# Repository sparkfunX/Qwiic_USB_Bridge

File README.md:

SparkFun Qwiic USB Development Kit - SAMD21
========================================

[*Qwiic USB Development Kit - SAMD21 (SPX-24639)*](https://www.sparkfun.com/products/24639)

The Qwiic USB Development kit is designed for folks that want to interface a Qwiic device quickly and easily to a computer. The core processor is the SAM21 which allows quick (hah!) and seamless serial printing over USB, as well as easy development and programming using the Arduino environment. The professional printed enclosure makes the device easy to plug/unplug as well as allowing Qwiic boards to be mounted to the enclosure itself.

The development kit features two Qwiic connectors and a user-addressable WS2812 LED. In case you need more IO, there are four GPIO pins, accessible by removing the enclosure, two of which are ADC pins. This little device is not only a great tool for making compact prototypes, but a handy way to add Qwiic sensors to your PC-based projects.

Repository Contents
-------------------

* **/Documentation** - Data sheets, additional product information
* **/Enclosure** - Enclosure files 
* **/Firmware** - Example code 
* **/Hardware** - Eagle design files (.brd, .sch)
* **/Production** - Production panel files (.brd)

License Information
-------------------

This product is _**open source**_! 

Please review the LICENSE.md file for license information. 

If you have any questions or concerns on licensing, please contact technical support on our [SparkFun forums](https://forum.sparkfun.com/viewforum.php?f=152).

Distributed as-is; no warranty is given.

- Your friends at SparkFun.

_<COLLABORATION CREDIT>_

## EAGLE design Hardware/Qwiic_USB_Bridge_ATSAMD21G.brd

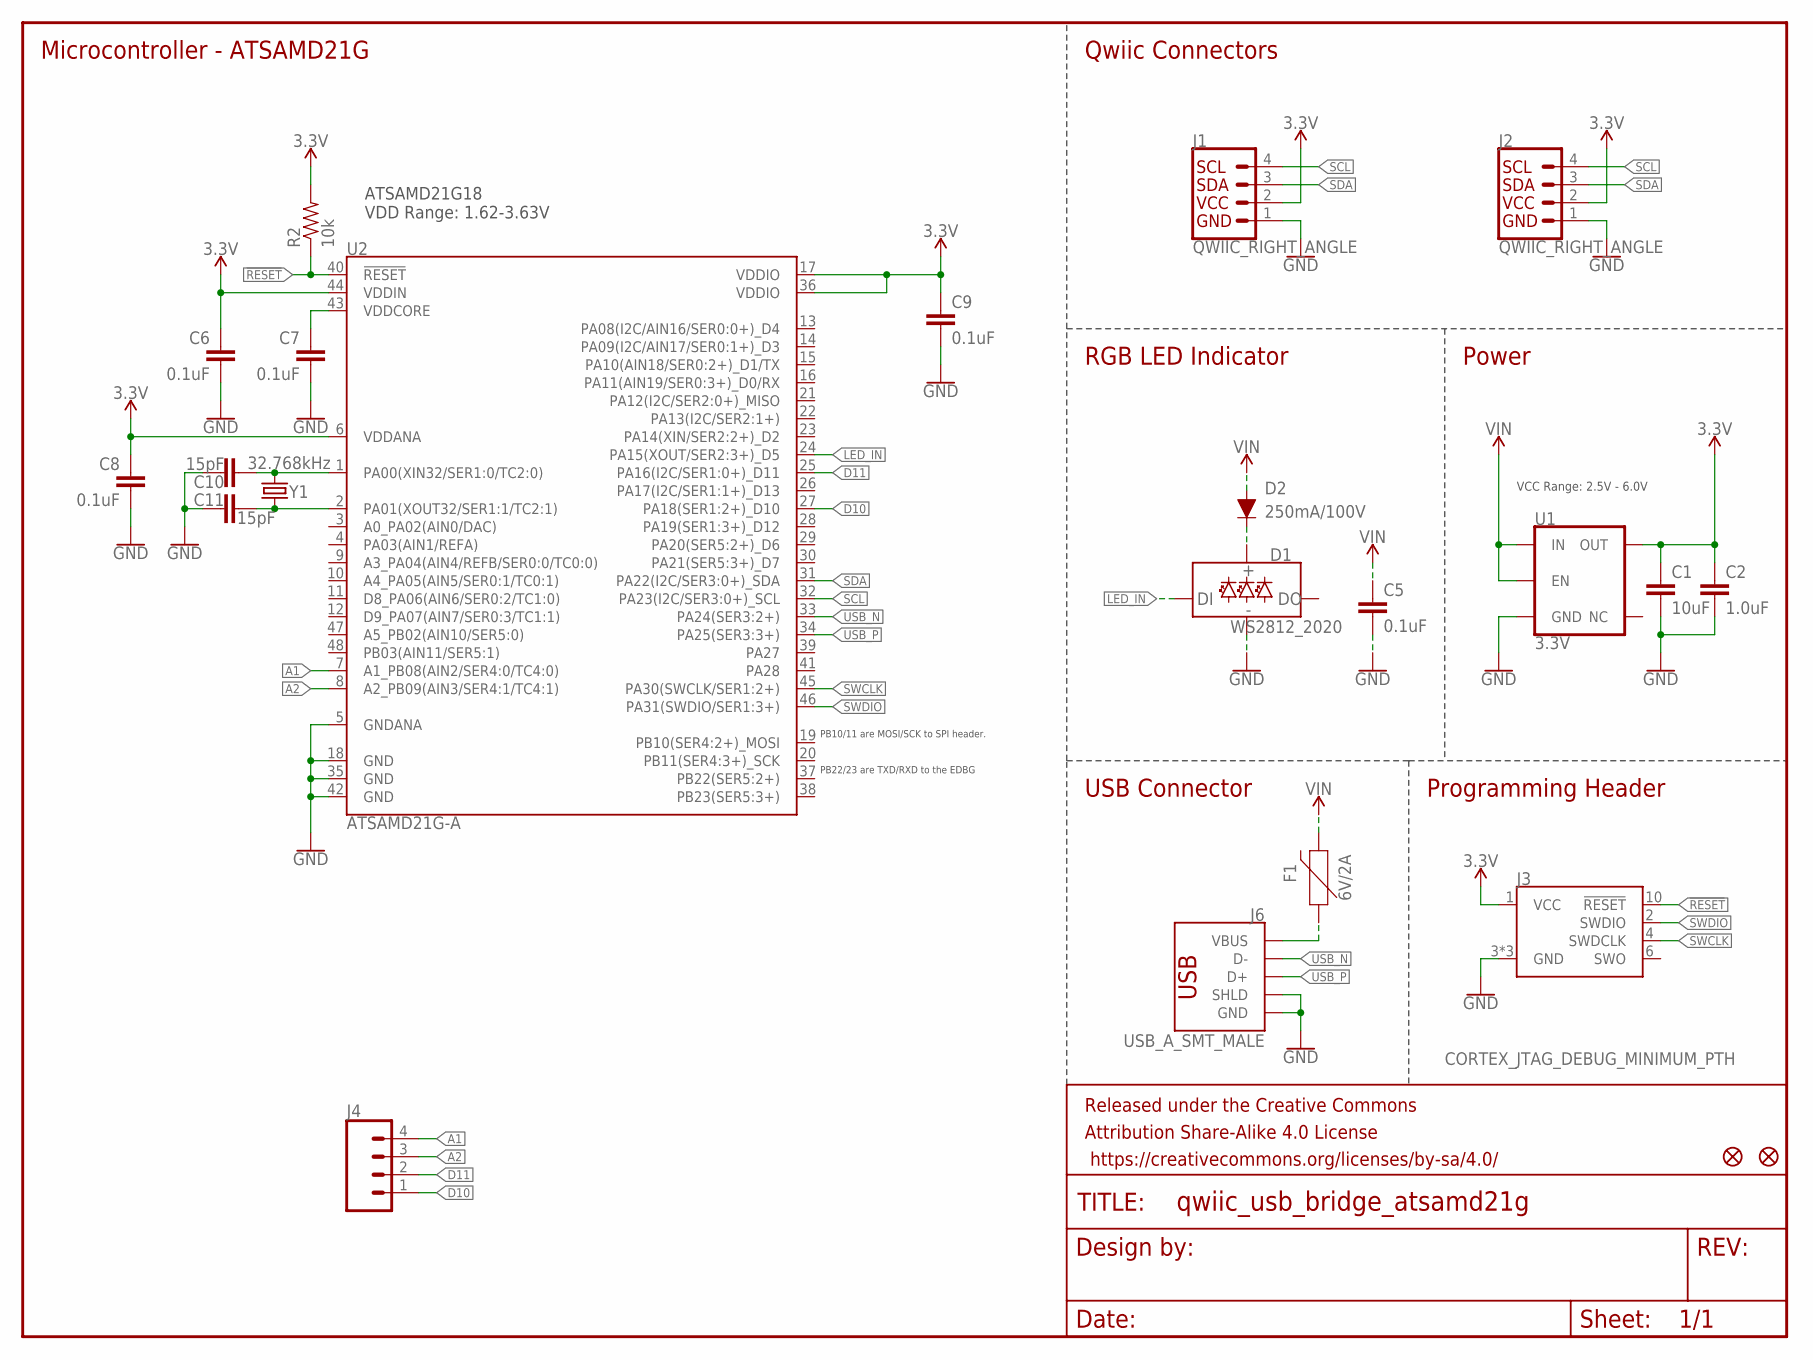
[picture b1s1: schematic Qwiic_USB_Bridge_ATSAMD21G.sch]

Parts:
C1: 10uF; 0603
C2: 1.0uF; 0603
C5, C6, C7, C8, C9: 0.1uF; 0603
C10, C11: 15pF; 0603
D1: WS2812_2020; WS2812-2020
D2: 250mA/100V; SOD-323
F1: 6V/2A; 1210
FD1, FD2: FIDUCIALUFIDUCIAL; FIDUCIAL-MICRO
FRAME2: FRAME-LETTER; CREATIVE_COMMONS
J1, J2: QWIIC_RIGHT_ANGLE; JST04_1MM_RA
J3: CORTEX_JTAG_DEBUG_MINIMUM_PTH; 2X5-PTH-1.27MM
J4: CONN_041X04_NO_SILK; 1X04_NO_SILK
J6: USB_A_SMT_MALE; USB-A-SMT-MALE
R2: 10k; 0603
U1: 3.3V; SOT23-5
U2: ATSAMD21G-A; TQFP-48
Y1: 32.768kHz; CRYSTAL-SMD-3.2X1.5MM

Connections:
3.3V: C1.1, C2.1, C6.1, C8.1, C9.1, J1.2, J2.2, J3.1 (VCC), R2.2, U1.5 (OUT), U2.6 (VDDANA), U2.17 (VDDIO), U2.36 (VDDIO), U2.44 (VDDIN)
!RESET: J3.10 (!RESET), R2.1, U2.40 (!RESET!)
A1: J4.4, U2.7 (A1_PB08(AIN2/SER4:0/TC4:0))
A2: J4.3, U2.8 (A2_PB09(AIN3/SER4:1/TC4:1))
D10: J4.1, U2.27 (PA18(SER1:2+)_D10)
D11: J4.2, U2.25 (PA16(I2C/SER1:0+)_D11)
GND: C1.2, C2.2, C5.2, C6.2, C7.2, C8.2, C9.2, C10.1, C11.2, D1.GND, J1.1, J2.1, J3.3 (GND), J3.5 (GND), J3.9 (GND), J6.GND1 (GND), J6.SHLD1 (SHLD), J6.SHLD2 (SHLD), U1.2 (GND), U2.5 (GNDANA), U2.18 (GND), U2.35 (GND), U2.42 (GND)
LED_IN: D1.DI, U2.24 (PA15(XOUT/SER2:3+)_D5)
unnamed: F1.1, J6.VBUS1 (VBUS)
unnamed: D1.VCC, D2.C
unnamed: C10.2, U2.1 (PA00(XIN32/SER1:0/TC2:0)), Y1.P$2 (2)
unnamed: C11.1, U2.2 (PA01(XOUT32/SER1:1/TC2:1)), Y1.P$1 (1)
SCL: J1.4, J2.4, U2.32 (PA23(I2C/SER3:0+)_SCL)
SDA: J1.3, J2.3, U2.31 (PA22(I2C/SER3:0+)_SDA)
SWCLK: J3.4 (SWDCLK), U2.45 (PA30(SWCLK/SER1:2+))
SWDIO: J3.2 (SWDIO), U2.46 (PA31(SWDIO/SER1:3+))
USB_N: J6.D-1 (D-), U2.33 (PA24(SER3:2+))
USB_P: J6.D+1 (D+), U2.34 (PA25(SER3:3+))
VDDCORE1: C7.1, U2.43 (VDDCORE)
VIN: C5.1, D2.A, F1.2, U1.1 (IN), U1.3 (EN)

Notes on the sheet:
Qwiic Connectors
RGB LED Indicator
Power
Microcontroller - ATSAMD21G
VCC Range: 2.5V - 6.0V
USB Connector
Programming Header
PB22/23 are TXD/RXD to the EDBG
PB10/11 are MOSI/SCK to SPI header.
ATSAMD21G18 VDD Range: 1.62-3.63V

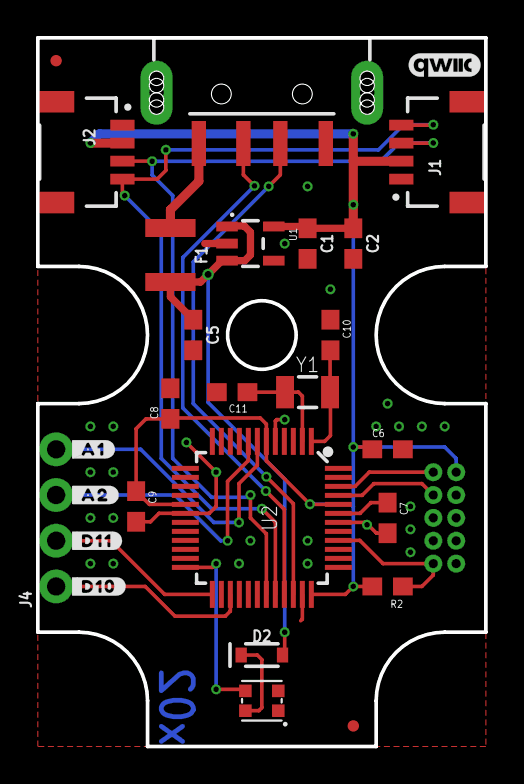
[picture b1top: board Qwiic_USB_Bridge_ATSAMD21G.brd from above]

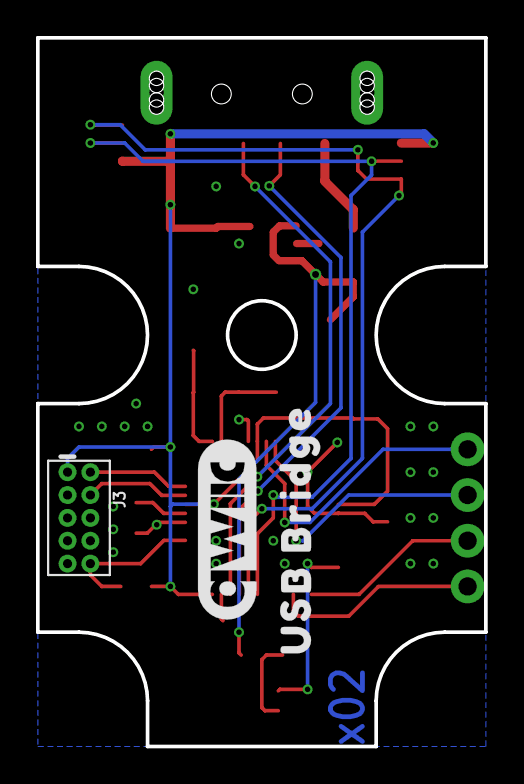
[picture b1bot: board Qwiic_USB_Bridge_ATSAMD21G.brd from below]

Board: 2 copper layers, 24.9 x 39.4 mm, 31 parts (3 on the bottom side), 20 nets.

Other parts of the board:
U$1: #_A1#0
U$2: #_A2#0
U$3: #_D11#0
U$4: #_D10#0
U$7: QWIIC_10MM
U$8: USB_BRIDGE0
U$9: QWIIC_4MM

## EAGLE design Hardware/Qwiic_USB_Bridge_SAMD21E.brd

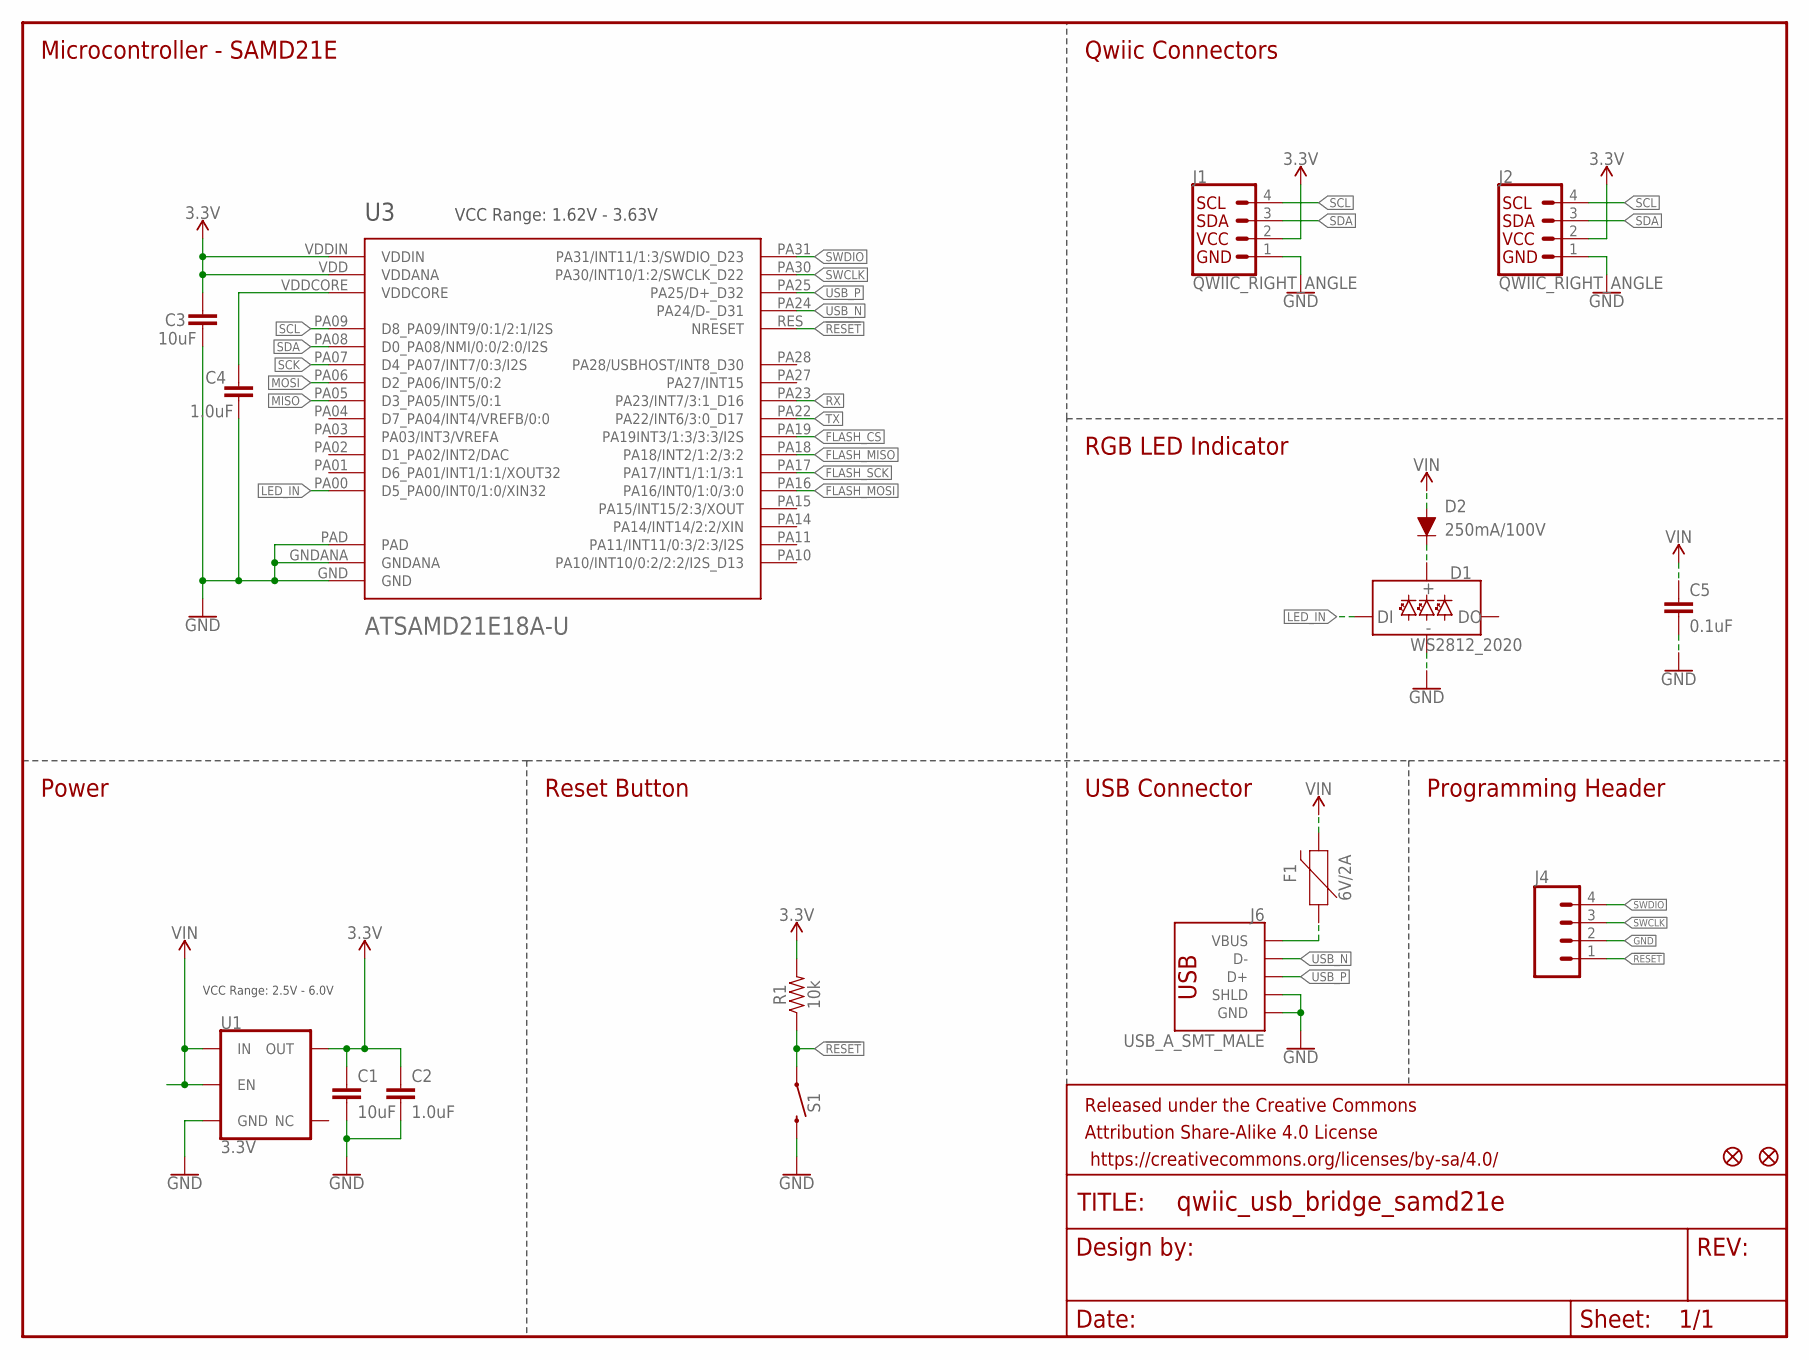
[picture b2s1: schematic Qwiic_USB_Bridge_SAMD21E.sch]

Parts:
C1, C3: 10uF; 0603
C2, C4: 1.0uF; 0402
C5: 0.1uF; 0603
D1: WS2812_2020; WS2812-2020
D2: 250mA/100V; SOD-323
F1: 6V/2A; 1210
FD1, FD2: FIDUCIALUFIDUCIAL; FIDUCIAL-MICRO
FRAME2: FRAME-LETTER; CREATIVE_COMMONS
J1, J2: QWIIC_RIGHT_ANGLE; JST04_1MM_RA
J4: CONN_041.27MM_NO_SILK; 1X04_1.27MM_NO_SILK
J6: USB_A_SMT_MALE; USB-A-SMT-MALE
R1: 10k; 0603
S1: MOMENTARY-SWITCH-SPST-SMD-6.0X3.5MM; TACTILE_SWITCH_SMD_6.0X3.5MM
U1: 3.3V; SOT23-5
U3: ATSAMD21E18A-U; QFN-32_SAMD

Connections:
3.3V: C1.1, C2.1, C3.1, J1.2, J2.2, R1.2, U1.5 (OUT), U3.VDD (VDDANA), U3.VDDIN
!RESET: J4.1, R1.1, S1.1, U3.RES (NRESET)
FLASH_CS: U3.PA19 (PA19INT3/1:3/3:3/I2S)
FLASH_MISO: U3.PA18 (PA18/INT2/1:2/3:2)
FLASH_MOSI: U3.PA16 (PA16/INT0/1:0/3:0)
FLASH_SCK: U3.PA17 (PA17/INT1/1:1/3:1)
GND: C1.2, C2.2, C3.2, C4.1, C5.2, D1.GND, J1.1, J2.1, J4.2, J6.GND1 (GND), J6.SHLD1 (SHLD), J6.SHLD2 (SHLD), S1.2, U1.2 (GND), U3.GND, U3.GNDANA, U3.PAD
LED_IN: D1.DI, U3.PA00 (D5_PA00/INT0/1:0/XIN32)
MISO: U3.PA05 (D3_PA05/INT5/0:1)
MOSI: U3.PA06 (D2_PA06/INT5/0:2)
unnamed: F1.1, J6.VBUS1 (VBUS)
unnamed: D1.VCC, D2.C
RX: U3.PA23 (PA23/INT7/3:1_D16)
SCK: U3.PA07 (D4_PA07/INT7/0:3/I2S)
SCL: J1.4, J2.4, U3.PA09 (D8_PA09/INT9/0:1/2:1/I2S)
SDA: J1.3, J2.3, U3.PA08 (D0_PA08/NMI/0:0/2:0/I2S)
SWCLK: J4.3, U3.PA30 (PA30/INT10/1:2/SWCLK_D22)
SWDIO: J4.4, U3.PA31 (PA31/INT11/1:3/SWDIO_D23)
TX: U3.PA22 (PA22/INT6/3:0_D17)
USB_N: J6.D-1 (D-), U3.PA24 (PA24/D-_D31)
USB_P: J6.D+1 (D+), U3.PA25 (PA25/D+_D32)
VDDCORE: C4.2, U3.VDDCORE
VIN: C5.1, D2.A, F1.2, U1.1 (IN), U1.3 (EN)

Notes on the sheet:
Qwiic Connectors
RGB LED Indicator
Power
Microcontroller - SAMD21E
VCC Range: 2.5V - 6.0V
VCC Range: 1.62V - 3.63V
Reset Button
USB Connector
Programming Header

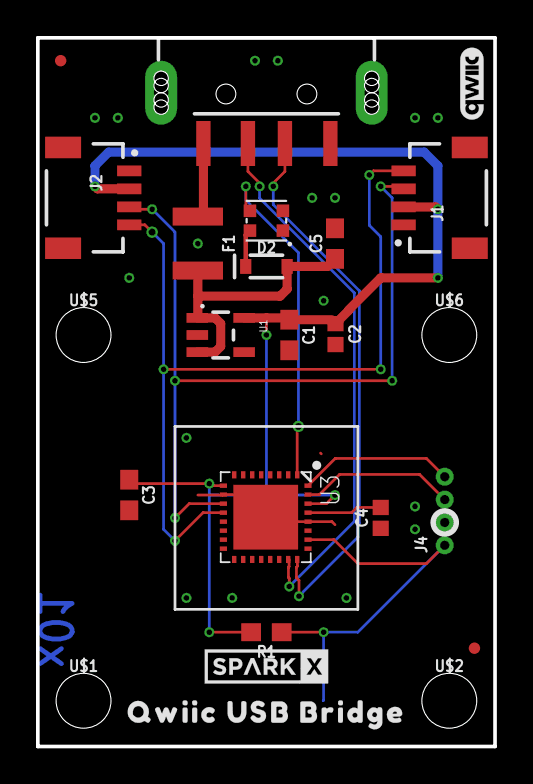
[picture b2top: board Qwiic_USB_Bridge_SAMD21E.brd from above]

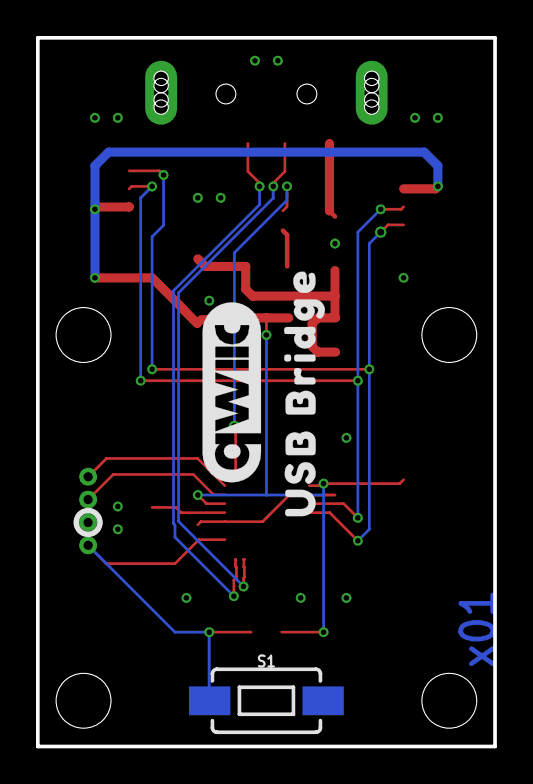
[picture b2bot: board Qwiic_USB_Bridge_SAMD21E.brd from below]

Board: 2 copper layers, 25.4 x 39.4 mm, 28 parts (3 on the bottom side), 14 nets.

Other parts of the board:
U$1, U$2, U$5, U$6: STAND-OFF-TIGHT
U$3: QWIIC_USB_BRIDGE0
U$4: SPARKX-SMALL
U$7: QWIIC_10MM
U$8: USB_BRIDGE0
U$9: QWIIC_4MM

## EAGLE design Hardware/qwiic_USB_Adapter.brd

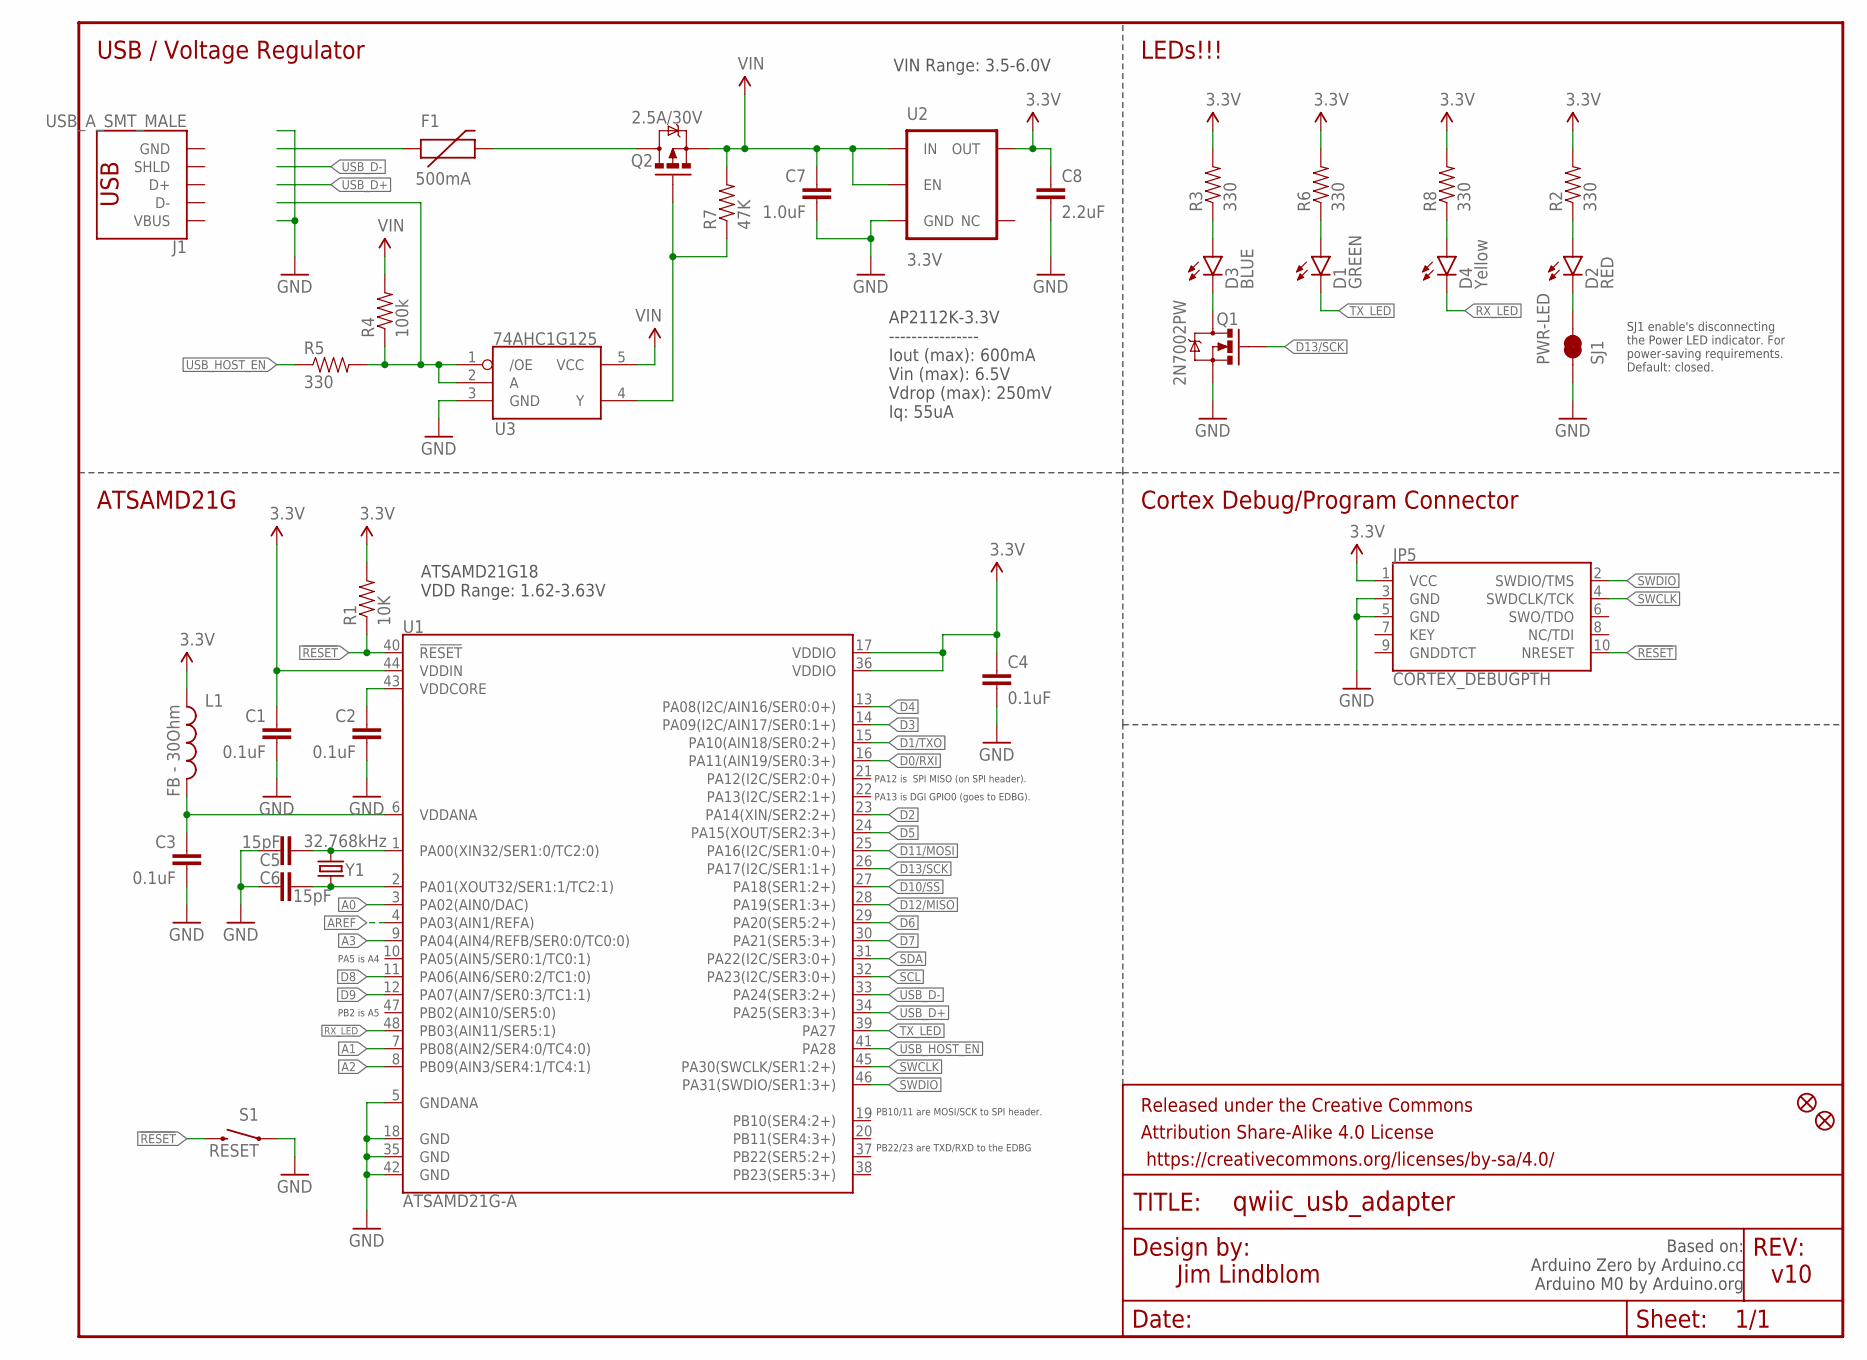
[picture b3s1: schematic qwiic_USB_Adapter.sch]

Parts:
C1, C2, C3, C4: 0.1uF; 0402-CAP
C5, C6: 15pF; 0402-CAP
C7: 1.0uF; 0805-CAP
C8: 2.2uF; 0603-CAP
D1: GREEN; LED-0603
D2: RED; LED-0603
D3: BLUE; LED-0603
D4: Yellow; LED-0603
F1: 500mA; PTC-1206
FID1, FID2: FIDUCIAL1X2; FIDUCIAL-1X2
FRAME1: FRAME-LETTER; CREATIVE_COMMONS
J1: USB_A_SMT_MALE; USB-A-SMT-MALE
JP5: CORTEX_DEBUGPTH; 2X5-PTH-1.27MM
L1: FB - 30Ohm; 0603
Q1: 2N7002PW; SOT323
Q2: 2.5A/30V; SOT23-3
R1: 10K; 0603-RES
R2, R3, R5, R6, R8: 330; 0603-RES
R4: 100k; 0603-RES
R7: 47K; 0603-RES
S1: RESET; TACTILE_SWITCH_SMD_4.6X2.8MM
SJ1: PWR-LED; PAD-JUMPER-2-NC_BY_TRACE_NO_SILK
U1: ATSAMD21G-A; TQFP-48
U2: 3.3V; SOT23-5
U3: 74AHC1G125; SOT23-5
Y1: 32.768kHz; CRYSTAL-SMD-3.2X1.5MM

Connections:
3.3V: C1.1, C4.1, C8.1, JP5.1 (VCC), L1.1, R1.2, R2.2, R3.2, R6.2, R8.2, U1.17 (VDDIO), U1.36 (VDDIO), U1.44 (VDDIN), U2.5 (OUT)
!RESET: JP5.10 (NRESET), R1.1, S1.3 (2), S1.4 (2), U1.40 (!RESET!)
A0: U1.3 (PA02(AIN0/DAC))
A1: U1.7 (PB08(AIN2/SER4:0/TC4:0))
A2: U1.8 (PB09(AIN3/SER4:1/TC4:1))
A3: U1.9 (PA04(AIN4/REFB/SER0:0/TC0:0))
AREF: U1.4 (PA03(AIN1/REFA))
D0/RXI: U1.16 (PA11(AIN19/SER0:3+))
D1/TXO: U1.15 (PA10(AIN18/SER0:2+))
D2: U1.23 (PA14(XIN/SER2:2+))
D3: U1.14 (PA09(I2C/AIN17/SER0:1+))
D4: U1.13 (PA08(I2C/AIN16/SER0:0+))
D5: U1.24 (PA15(XOUT/SER2:3+))
D6: U1.29 (PA20(SER5:2+))
D7: U1.30 (PA21(SER5:3+))
D8: U1.11 (PA06(AIN6/SER0:2/TC1:0))
D9: U1.12 (PA07(AIN7/SER0:3/TC1:1))
D10/SS: U1.27 (PA18(SER1:2+))
D11/MOSI: U1.25 (PA16(I2C/SER1:0+))
D12/MISO: U1.28 (PA19(SER1:3+))
D13/SCK: Q1.1 (G), U1.26 (PA17(I2C/SER1:1+))
GND: C1.2, C2.2, C3.2, C4.2, C5.1, C6.2, C7.2, C8.2, J1.GND1 (GND), JP5.3 (GND), JP5.5 (GND), Q1.2 (S), S1.1, S1.2 (1), SJ1.1, U1.5 (GNDANA), U1.18 (GND), U1.35 (GND), U1.42 (GND), U2.2 (GND), U3.3 (GND)
unnamed: C5.2, U1.1 (PA00(XIN32/SER1:0/TC2:0)), Y1.P$2 (2)
unnamed: D3.C, Q1.3 (D)
unnamed: C6.1, U1.2 (PA01(XOUT32/SER1:1/TC2:1)), Y1.P$1 (1)
unnamed: D2.A, R2.1
unnamed: D3.A, R3.1
unnamed: F1.2, Q2.3 (D)
unnamed: R4.1, R5.2, U3.1 (/OE), U3.2 (A)
unnamed: Q2.1 (G), R7.1, U3.4 (Y)
unnamed: D1.A, R6.1
unnamed: D4.A, R8.1
unnamed: D2.C, SJ1.2
RX_LED: D4.C, U1.48 (PB03(AIN11/SER5:1))
SCL: U1.32 (PA23(I2C/SER3:0+))
SDA: U1.31 (PA22(I2C/SER3:0+))
SWCLK: JP5.4 (SWDCLK/TCK), U1.45 (PA30(SWCLK/SER1:2+))
SWDIO: JP5.2 (SWDIO/TMS), U1.46 (PA31(SWDIO/SER1:3+))
TX_LED: D1.C, U1.39 (PA27)
USB_D+: U1.34 (PA25(SER3:3+))
USB_D-: U1.33 (PA24(SER3:2+))
USB_HOST_EN: R5.1, U1.41 (PA28)
VBUS: J1.VBUS1 (VBUS)
VDDANA: C3.1, L1.2, U1.6 (VDDANA)
VDDCORE: C2.1, U1.43 (VDDCORE)
VIN: C7.1, Q2.2 (S), R4.2, R7.2, U2.1 (IN), U2.3 (EN), U3.5 (VCC)

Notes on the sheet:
PB22/23 are TXD/RXD to the EDBG
PB10/11 are MOSI/SCK to SPI header.
PA12 is SPI MISO (on SPI header).
PA13 is DGI GPIO0 (goes to EDBG).
PA5 is A4
PB2 is A5
USB / Voltage Regulator
LEDs!!!
Cortex Debug/Program Connector
ATSAMD21G
Jim Lindblom
v10
ATSAMD21G18 VDD Range: 1.62-3.63V
SJ1 enable's disconnecting the Power LED indicator. For power-saving requirements. Default: closed.
VIN Range: 3.5-6.0V
Based on: Arduino Zero by Arduino.cc Arduino M0 by Arduino.org
AP2112K-3.3V ---------------- Iout (max): 600mA Vin (max): 6.5V Vdrop (max): 250mV Iq: 55uA

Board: 4 copper layers, 35 parts (1 on the bottom side), 23 nets, no tracks yet.

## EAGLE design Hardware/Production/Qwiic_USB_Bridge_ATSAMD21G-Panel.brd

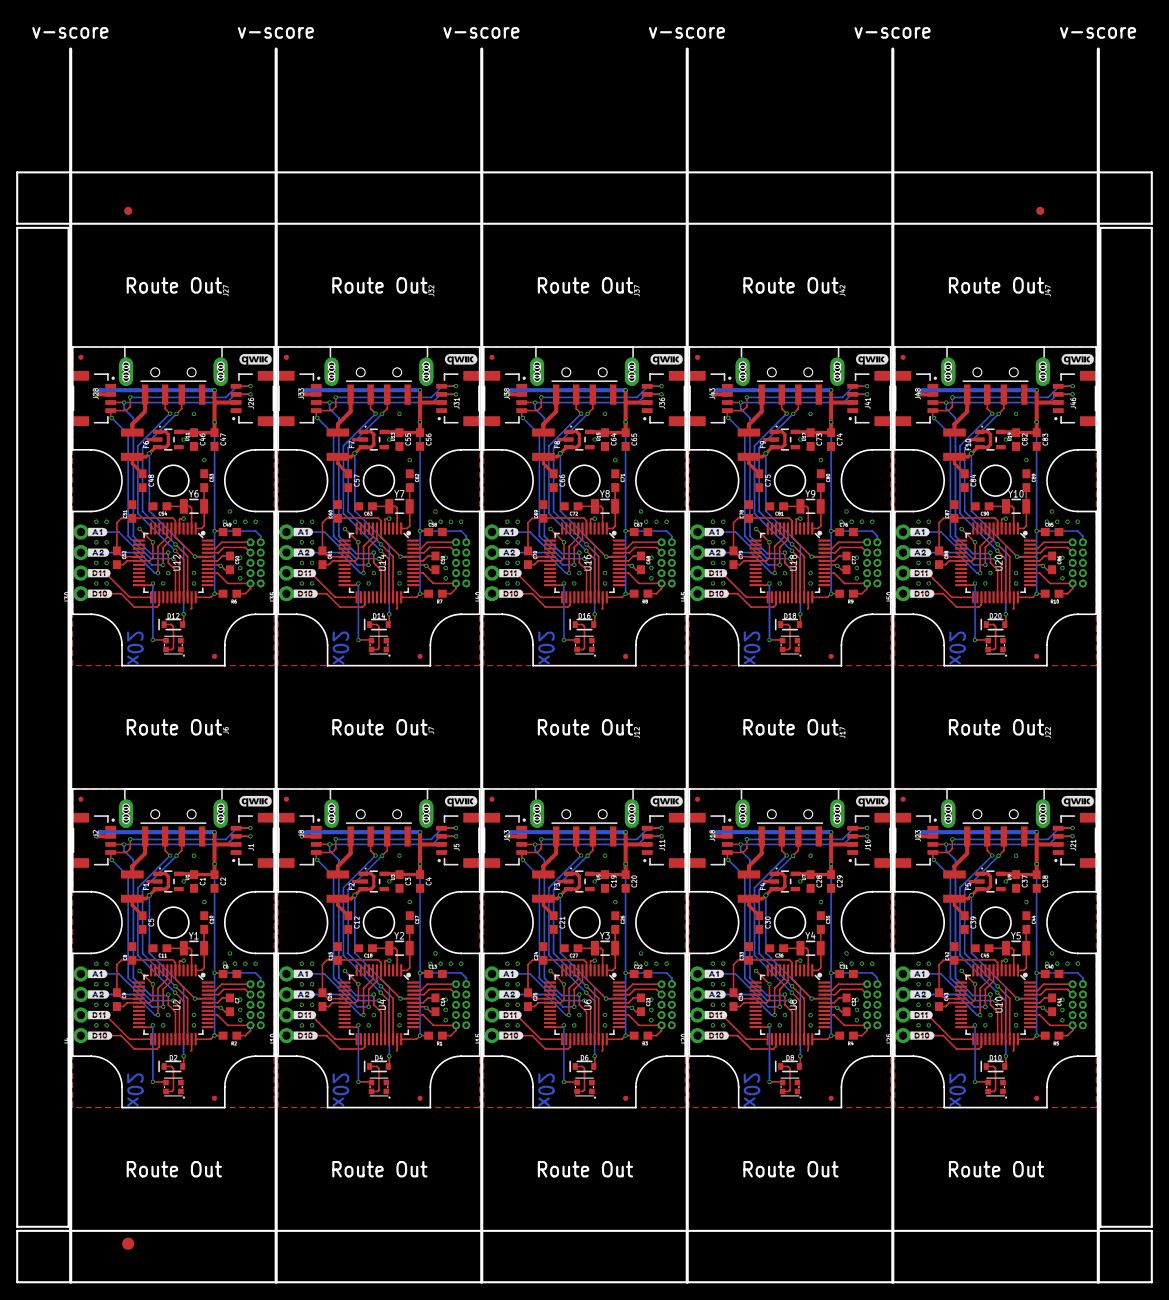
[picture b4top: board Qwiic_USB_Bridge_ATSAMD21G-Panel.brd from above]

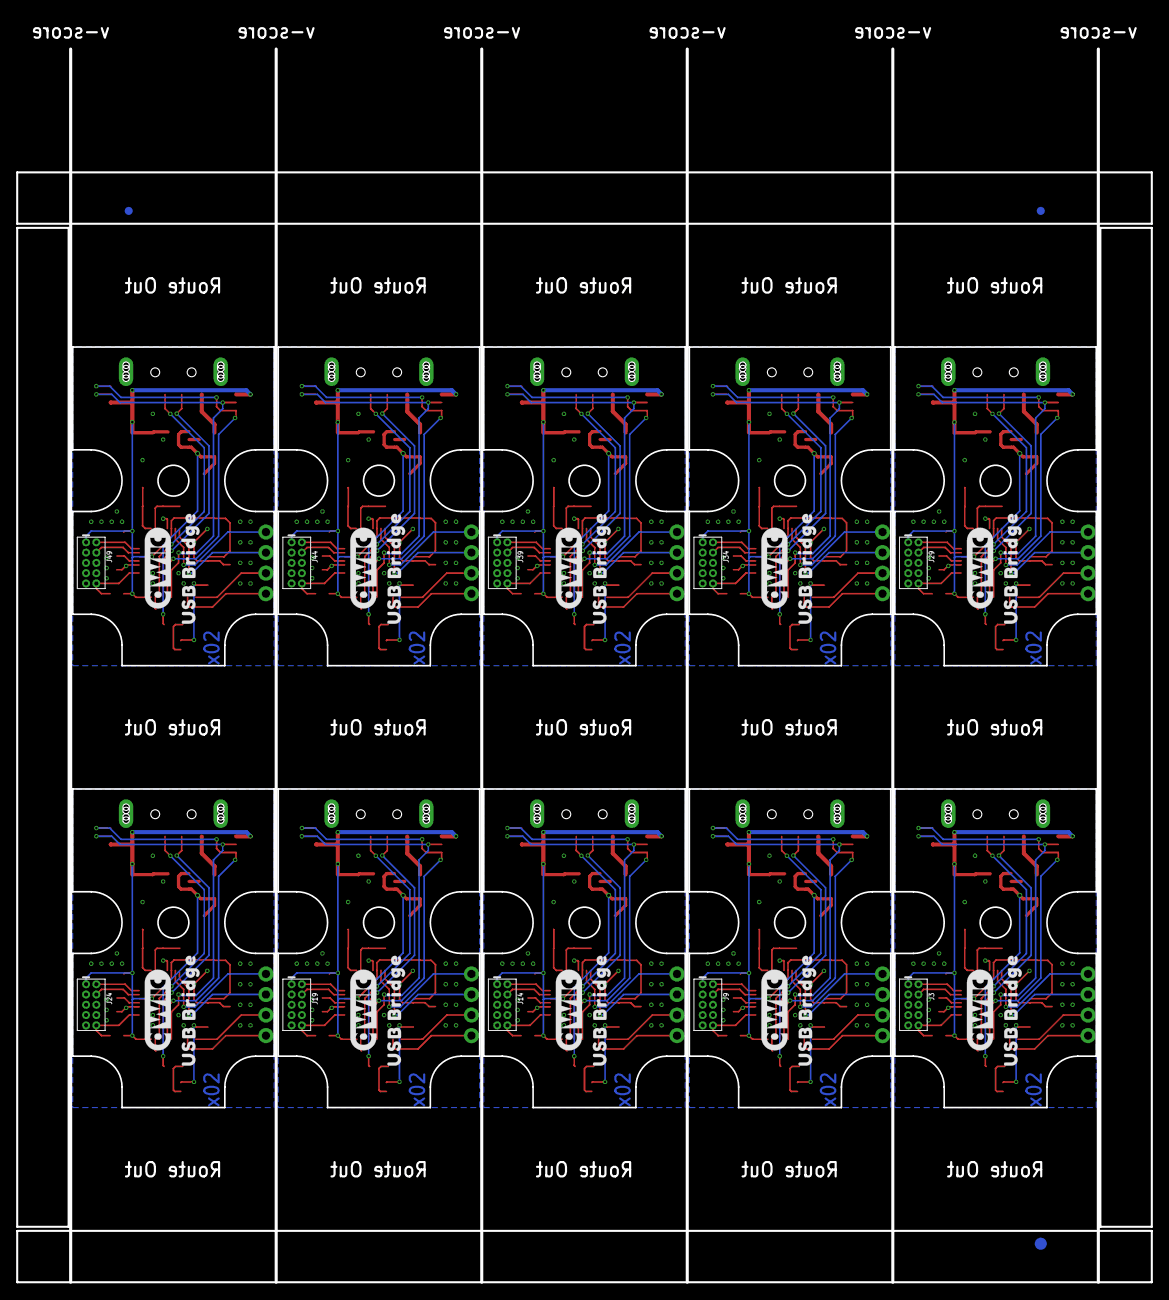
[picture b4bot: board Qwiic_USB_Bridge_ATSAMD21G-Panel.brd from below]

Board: 2 copper layers, 140.1 x 156.3 mm, 306 parts (33 on the bottom side), 200 nets.

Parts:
C1, C3, C19, C28, C37, C46, C55, C64, C73, C82: 10uF; 0603
C2, C4, C20, C29, C38, C47, C56, C65, C74, C83: 1.0uF; 0603
C5, C6, C7, C8, C9, C12, C13, C14, C15, C16, C21, C22, C23, C24, C25, C30, C31, C32, C33, C34, C39, C40, C41, C42, C43, C48, C49, C50, C51, C52, C57, C58, C59, C60, C61, C66, C67, C68, C69, C70, C75, C76, C77, C78, C79, C84, C85, C86, C87, C88: 0.1uF; 0603
C10, C11, C17, C18, C26, C27, C35, C36, C44, C45, C53, C54, C62, C63, C71, C72, C80, C81, C89, C90: 15pF; 0603
D1, D3, D5, D7, D9, D11, D13, D15, D17, D19: WS2812_2020; WS2812-2020
D2, D4, D6, D8, D10, D12, D14, D16, D18, D20: 250mA/100V; SOD-323
E$1, E$2, E$3, E$4: FIDUCIAL-1X2
E$5, E$6: FIDUCIAL-1.5X3
F1, F2, F3, F4, F5, F6, F7, F8, F9, F10: 6V/2A; 1210
FD1, FD2, FD3, FD4, FD5, FD6, FD7, FD8, FD9, FD10, FD11, FD12, FD13, FD14, FD15, FD16, FD17, FD18, FD19, FD20: FIDUCIALUFIDUCIAL; FIDUCIAL-MICRO
J1, J2, J5, J8, J11, J13, J16, J18, J21, J23, J26, J28, J31, J33, J36, J38, J41, J43, J46, J48: QWIIC_RIGHT_ANGLE; JST04_1MM_RA
J3, J9, J14, J19, J24, J29, J34, J39, J44, J49: CORTEX_JTAG_DEBUG_MINIMUM_PTH; 2X5-PTH-1.27MM
J4, J10, J15, J20, J25, J30, J35, J40, J45, J50: 1X04_NO_SILK
J6, J7, J12, J17, J22, J27, J32, J37, J42, J47: USB_A_SMT_MALE; USB-A-SMT-MALE
R1, R2, R3, R4, R5, R6, R7, R8, R9, R10: 10k; 0603
U1, U3, U5, U7, U9, U11, U13, U15, U17, U19: 3.3V; SOT23-5
U2, U4, U6, U8, U10, U12, U14, U16, U18, U20: ATSAMD21G-A; TQFP-48
U$1, U$11, U$18, U$25, U$32, U$39, U$46, U$53, U$60, U$67: #_A1#0
U$2, U$12, U$19, U$26, U$33, U$40, U$47, U$54, U$61, U$68: #_A2#0
U$3, U$13, U$20, U$27, U$34, U$41, U$48, U$55, U$62, U$69: #_D11#0
U$4, U$14, U$21, U$28, U$35, U$42, U$49, U$56, U$63, U$70: #_D10#0
U$5, U$7, U$15, U$22, U$29, U$36, U$43, U$50, U$57, U$64: QWIIC_10MM
U$6, U$8, U$16, U$23, U$30, U$37, U$44, U$51, U$58, U$65: USB_BRIDGE0
U$9, U$10, U$17, U$24, U$31, U$38, U$45, U$52, U$59, U$66: QWIIC_4MM
Y1, Y2, Y3, Y4, Y5, Y6, Y7, Y8, Y9, Y10: 32.768kHz; CRYSTAL-SMD-3.2X1.5MM

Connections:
3.3V: C1.1, C2.1, C6.1, C8.1, C9.1, J1.2, J2.2, J3.1, R2.2, U1.5, U2.6, U2.17, U2.36, U2.44
3.3V1: C3.1, C4.1, C13.1, C15.1, C16.1, J5.2, J8.2, J9.1, R1.2, U3.5, U4.6, U4.17, U4.36, U4.44
3.3V2: C19.1, C20.1, C22.1, C24.1, C25.1, J11.2, J13.2, J14.1, R3.2, U5.5, U6.6, U6.17, U6.36, U6.44
3.3V3: C28.1, C29.1, C31.1, C33.1, C34.1, J16.2, J18.2, J19.1, R4.2, U7.5, U8.6, U8.17, U8.36, U8.44
3.3V4: C37.1, C38.1, C40.1, C42.1, C43.1, J21.2, J23.2, J24.1, R5.2, U9.5, U10.6, U10.17, U10.36, U10.44
3.3V5: C46.1, C47.1, C49.1, C51.1, C52.1, J26.2, J28.2, J29.1, R6.2, U11.5, U12.6, U12.17, U12.36, U12.44
3.3V6: C55.1, C56.1, C58.1, C60.1, C61.1, J31.2, J33.2, J34.1, R7.2, U13.5, U14.6, U14.17, U14.36, U14.44
3.3V7: C64.1, C65.1, C67.1, C69.1, C70.1, J36.2, J38.2, J39.1, R8.2, U15.5, U16.6, U16.17, U16.36, U16.44
3.3V8: C73.1, C74.1, C76.1, C78.1, C79.1, J41.2, J43.2, J44.1, R9.2, U17.5, U18.6, U18.17, U18.36, U18.44
3.3V9: C82.1, C83.1, C85.1, C87.1, C88.1, J46.2, J48.2, J49.1, R10.2, U19.5, U20.6, U20.17, U20.36, U20.44
!RESET: J3.10, R2.1, U2.40
!RESET1: J9.10, R1.1, U4.40
!RESET2: J14.10, R3.1, U6.40
!RESET3: J19.10, R4.1, U8.40
!RESET4: J24.10, R5.1, U10.40
!RESET5: J29.10, R6.1, U12.40
!RESET6: J34.10, R7.1, U14.40
!RESET7: J39.10, R8.1, U16.40
!RESET8: J44.10, R9.1, U18.40
!RESET9: J49.10, R10.1, U20.40
A1: J4.4, U2.7
A2: J4.3, U2.8
A3: J10.4, U4.7
A4: J10.3, U4.8
A5: J15.4, U6.7
A6: J15.3, U6.8
A7: J20.4, U8.7
A8: J20.3, U8.8
A9: J25.4, U10.7
A10: J25.3, U10.8
A11: J30.4, U12.7
A12: J30.3, U12.8
A13: J35.4, U14.7
A14: J35.3, U14.8
A15: J40.4, U16.7
A16: J40.3, U16.8
A17: J45.4, U18.7
A18: J45.3, U18.8
A19: J50.4, U20.7
A20: J50.3, U20.8
D1: J10.2, U4.25
D2: J10.1, U4.27
D3: J15.2, U6.25
D4: J15.1, U6.27
D5: J20.2, U8.25
D6: J20.1, U8.27
D7: J25.2, U10.25
D8: J25.1, U10.27
D9: J30.2, U12.25
D10: J4.1, U2.27
D11: J4.2, U2.25
D12: J30.1, U12.27
D13: J35.2, U14.25
D14: J35.1, U14.27
D15: J40.2, U16.25
D16: J40.1, U16.27
D17: J45.2, U18.25
D18: J45.1, U18.27
D19: J50.2, U20.25
D20: J50.1, U20.27
GND: C1.2, C2.2, C5.2, C6.2, C7.2, C8.2, C9.2, C10.1, C11.2, D1.GND, J1.1, J2.1, J3.3, J3.5, J3.9, J6.GND1, J6.SHLD1, J6.SHLD2, U1.2, U2.5, U2.18, U2.35, U2.42
GND1: C3.2, C4.2, C12.2, C13.2, C14.2, C15.2, C16.2, C17.1, C18.2, D3.GND, J5.1, J7.GND1, J7.SHLD1, J7.SHLD2, J8.1, J9.3, J9.5, J9.9, U3.2, U4.5, U4.18, U4.35, U4.42
GND2: C19.2, C20.2, C21.2, C22.2, C23.2, C24.2, C25.2, C26.1, C27.2, D5.GND, J11.1, J12.GND1, J12.SHLD1, J12.SHLD2, J13.1, J14.3, J14.5, J14.9, U5.2, U6.5, U6.18, U6.35, U6.42
GND3: C28.2, C29.2, C30.2, C31.2, C32.2, C33.2, C34.2, C35.1, C36.2, D7.GND, J16.1, J17.GND1, J17.SHLD1, J17.SHLD2, J18.1, J19.3, J19.5, J19.9, U7.2, U8.5, U8.18, U8.35, U8.42
GND4: C37.2, C38.2, C39.2, C40.2, C41.2, C42.2, C43.2, C44.1, C45.2, D9.GND, J21.1, J22.GND1, J22.SHLD1, J22.SHLD2, J23.1, J24.3, J24.5, J24.9, U9.2, U10.5, U10.18, U10.35, U10.42
GND5: C46.2, C47.2, C48.2, C49.2, C50.2, C51.2, C52.2, C53.1, C54.2, D11.GND, J26.1, J27.GND1, J27.SHLD1, J27.SHLD2, J28.1, J29.3, J29.5, J29.9, U11.2, U12.5, U12.18, U12.35, U12.42
GND6: C55.2, C56.2, C57.2, C58.2, C59.2, C60.2, C61.2, C62.1, C63.2, D13.GND, J31.1, J32.GND1, J32.SHLD1, J32.SHLD2, J33.1, J34.3, J34.5, J34.9, U13.2, U14.5, U14.18, U14.35, U14.42
GND7: C64.2, C65.2, C66.2, C67.2, C68.2, C69.2, C70.2, C71.1, C72.2, D15.GND, J36.1, J37.GND1, J37.SHLD1, J37.SHLD2, J38.1, J39.3, J39.5, J39.9, U15.2, U16.5, U16.18, U16.35, U16.42
GND8: C73.2, C74.2, C75.2, C76.2, C77.2, C78.2, C79.2, C80.1, C81.2, D17.GND, J41.1, J42.GND1, J42.SHLD1, J42.SHLD2, J43.1, J44.3, J44.5, J44.9, U17.2, U18.5, U18.18, U18.35, U18.42
GND9: C82.2, C83.2, C84.2, C85.2, C86.2, C87.2, C88.2, C89.1, C90.2, D19.GND, J46.1, J47.GND1, J47.SHLD1, J47.SHLD2, J48.1, J49.3, J49.5, J49.9, U19.2, U20.5, U20.18, U20.35, U20.42
LED_IN: D1.DI, U2.24
LED_IN1: D3.DI, U4.24
LED_IN2: D5.DI, U6.24
LED_IN3: D7.DI, U8.24
LED_IN4: D9.DI, U10.24
LED_IN5: D11.DI, U12.24
LED_IN6: D13.DI, U14.24
LED_IN7: D15.DI, U16.24
LED_IN8: D17.DI, U18.24
LED_IN9: D19.DI, U20.24
unnamed: F1.1, J6.VBUS1
unnamed: D1.VCC, D2.C
unnamed: C10.2, U2.1, Y1.P$2
unnamed: C11.1, U2.2, Y1.P$1
unnamed: D3.VCC, D4.C
unnamed: F2.1, J7.VBUS1
unnamed: C17.2, U4.1, Y2.P$2
unnamed: C18.1, U4.2, Y2.P$1
unnamed: D5.VCC, D6.C
unnamed: F3.1, J12.VBUS1
unnamed: C26.2, U6.1, Y3.P$2
unnamed: C27.1, U6.2, Y3.P$1
unnamed: D7.VCC, D8.C
unnamed: F4.1, J17.VBUS1
unnamed: C35.2, U8.1, Y4.P$2
unnamed: C36.1, U8.2, Y4.P$1
unnamed: D9.VCC, D10.C
unnamed: F5.1, J22.VBUS1
unnamed: C44.2, U10.1, Y5.P$2
unnamed: C45.1, U10.2, Y5.P$1
unnamed: D11.VCC, D12.C
unnamed: F6.1, J27.VBUS1
unnamed: C53.2, U12.1, Y6.P$2
unnamed: C54.1, U12.2, Y6.P$1
unnamed: D13.VCC, D14.C
unnamed: F7.1, J32.VBUS1
unnamed: C62.2, U14.1, Y7.P$2
unnamed: C63.1, U14.2, Y7.P$1
unnamed: D15.VCC, D16.C
unnamed: F8.1, J37.VBUS1
unnamed: C71.2, U16.1, Y8.P$2
unnamed: C72.1, U16.2, Y8.P$1
unnamed: D17.VCC, D18.C
unnamed: F9.1, J42.VBUS1
unnamed: C80.2, U18.1, Y9.P$2
unnamed: C81.1, U18.2, Y9.P$1
unnamed: D19.VCC, D20.C
unnamed: F10.1, J47.VBUS1
unnamed: C89.2, U20.1, Y10.P$2
unnamed: C90.1, U20.2, Y10.P$1
SCL: J1.4, J2.4, U2.32
SCL1: J5.4, J8.4, U4.32
SCL2: J11.4, J13.4, U6.32
SCL3: J16.4, J18.4, U8.32
SCL4: J21.4, J23.4, U10.32
SCL5: J26.4, J28.4, U12.32
SCL6: J31.4, J33.4, U14.32
SCL7: J36.4, J38.4, U16.32
SCL8: J41.4, J43.4, U18.32
SCL9: J46.4, J48.4, U20.32
SDA: J1.3, J2.3, U2.31
SDA1: J5.3, J8.3, U4.31
SDA2: J11.3, J13.3, U6.31
SDA3: J16.3, J18.3, U8.31
SDA4: J21.3, J23.3, U10.31
SDA5: J26.3, J28.3, U12.31
SDA6: J31.3, J33.3, U14.31
SDA7: J36.3, J38.3, U16.31
SDA8: J41.3, J43.3, U18.31
SDA9: J46.3, J48.3, U20.31
SWCLK: J3.4, U2.45
SWCLK1: J9.4, U4.45
SWCLK2: J14.4, U6.45
SWCLK3: J19.4, U8.45
SWCLK4: J24.4, U10.45
SWCLK5: J29.4, U12.45
SWCLK6: J34.4, U14.45
SWCLK7: J39.4, U16.45
SWCLK8: J44.4, U18.45
SWCLK9: J49.4, U20.45
SWDIO: J3.2, U2.46
SWDIO1: J9.2, U4.46
SWDIO2: J14.2, U6.46
SWDIO3: J19.2, U8.46
SWDIO4: J24.2, U10.46
SWDIO5: J29.2, U12.46
SWDIO6: J34.2, U14.46
SWDIO7: J39.2, U16.46
SWDIO8: J44.2, U18.46
SWDIO9: J49.2, U20.46
USB_N: J6.D-1, U2.33
USB_N1: J7.D-1, U4.33
USB_N2: J12.D-1, U6.33
USB_N3: J17.D-1, U8.33
USB_N4: J22.D-1, U10.33
USB_N5: J27.D-1, U12.33
USB_N6: J32.D-1, U14.33
USB_N7: J37.D-1, U16.33
USB_N8: J42.D-1, U18.33
USB_N9: J47.D-1, U20.33
USB_P: J6.D+1, U2.34
USB_P1: J7.D+1, U4.34
USB_P2: J12.D+1, U6.34
USB_P3: J17.D+1, U8.34
USB_P4: J22.D+1, U10.34
USB_P5: J27.D+1, U12.34
USB_P6: J32.D+1, U14.34
USB_P7: J37.D+1, U16.34
USB_P8: J42.D+1, U18.34
USB_P9: J47.D+1, U20.34
VDDCORE1: C7.1, U2.43
VDDCORE2: C14.1, U4.43
VDDCORE3: C23.1, U6.43
VDDCORE4: C32.1, U8.43
VDDCORE5: C41.1, U10.43
VDDCORE6: C50.1, U12.43
VDDCORE7: C59.1, U14.43
VDDCORE8: C68.1, U16.43
VDDCORE9: C77.1, U18.43
VDDCORE10: C86.1, U20.43
VIN: C5.1, D2.A, F1.2, U1.1, U1.3
VIN1: C12.1, D4.A, F2.2, U3.1, U3.3
VIN2: C21.1, D6.A, F3.2, U5.1, U5.3
VIN3: C30.1, D8.A, F4.2, U7.1, U7.3
VIN4: C39.1, D10.A, F5.2, U9.1, U9.3
VIN5: C48.1, D12.A, F6.2, U11.1, U11.3
VIN6: C57.1, D14.A, F7.2, U13.1, U13.3
VIN7: C66.1, D16.A, F8.2, U15.1, U15.3
VIN8: C75.1, D18.A, F9.2, U17.1, U17.3
VIN9: C84.1, D20.A, F10.2, U19.1, U19.3

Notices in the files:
parts and their libraries:
SparkFun-Connectors: Licensing: Creative Commons ShareAlike 4.0 International - https://creativecommons.org/licenses/by-sa/4.0
SparkFun-Aesthetics: Released under the Creative Commons Attribution Share-Alike 4.0 License
SparkFun-Aesthetics: https://creativecommons.org/licenses/by-sa/4.0
